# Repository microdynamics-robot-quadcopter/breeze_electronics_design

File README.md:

# breeze_electronics_design

## Description
This project is created and managed by EDA softwares, which contains the breeze quadcopter's component library, footprint library, schematic, printed circuit boards, etc.

## Note
Because of the changes in the project's requirements, we decided to use **Altium Designer** as the tool for developing the first edition of PCB rather than **KiCad**! So if you want to find the latest PCB design documents, please visit the **altium** directory.

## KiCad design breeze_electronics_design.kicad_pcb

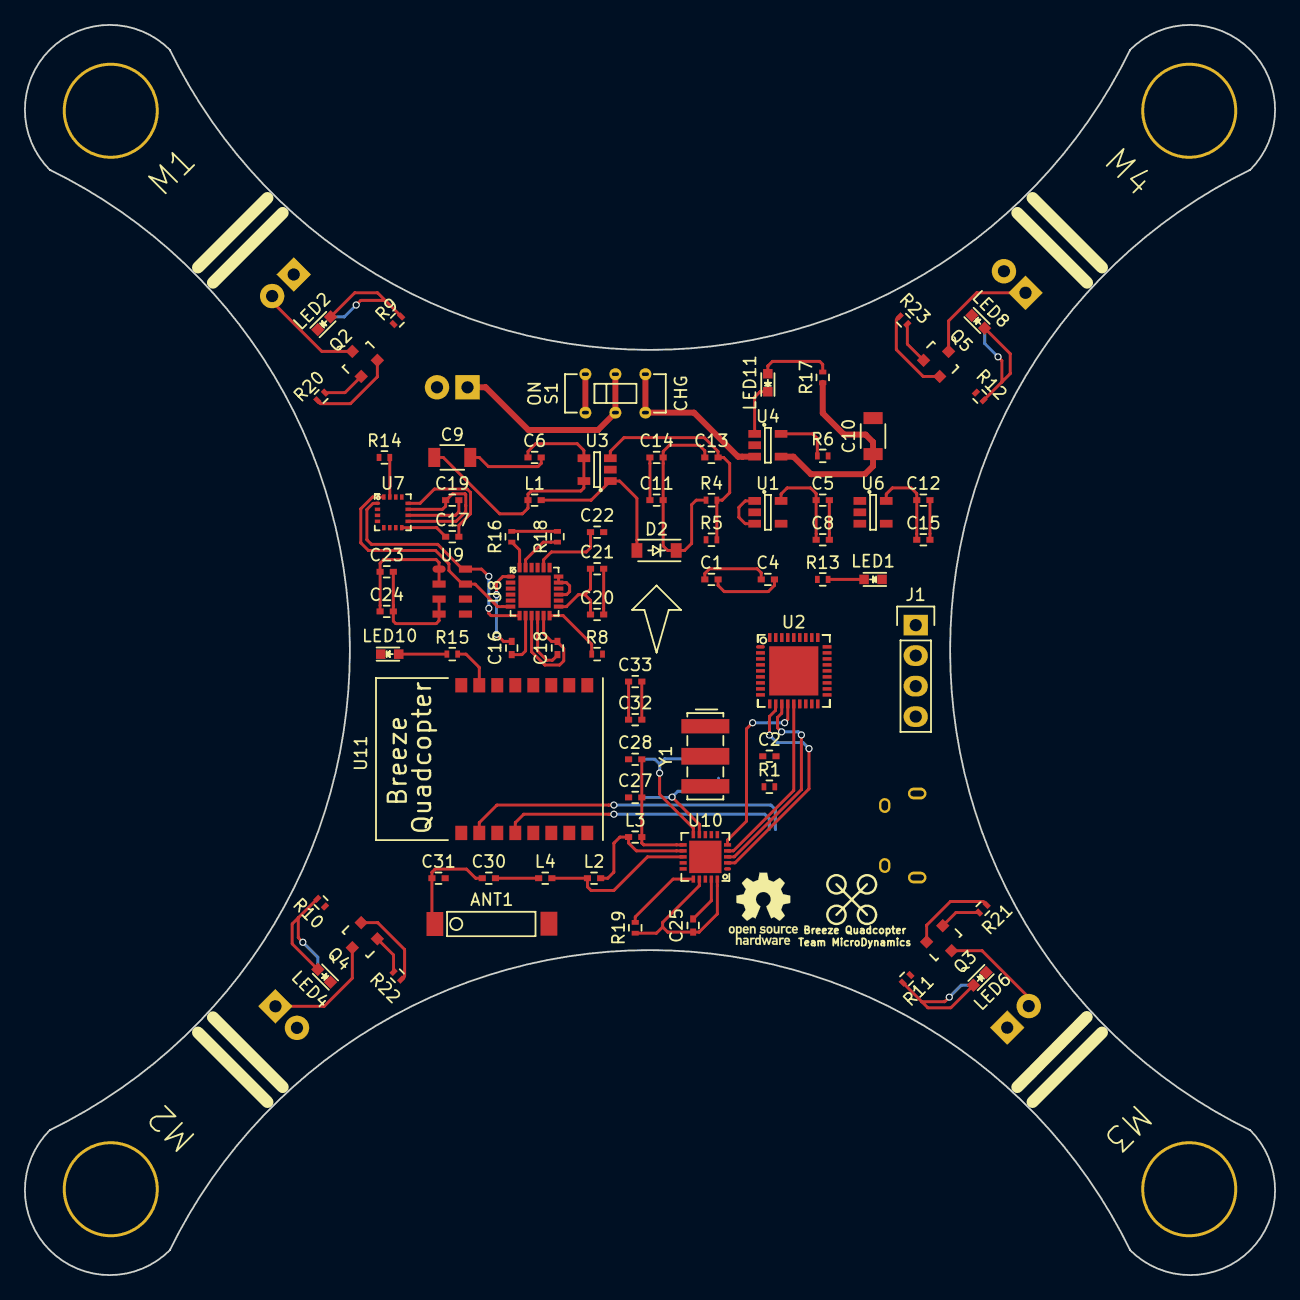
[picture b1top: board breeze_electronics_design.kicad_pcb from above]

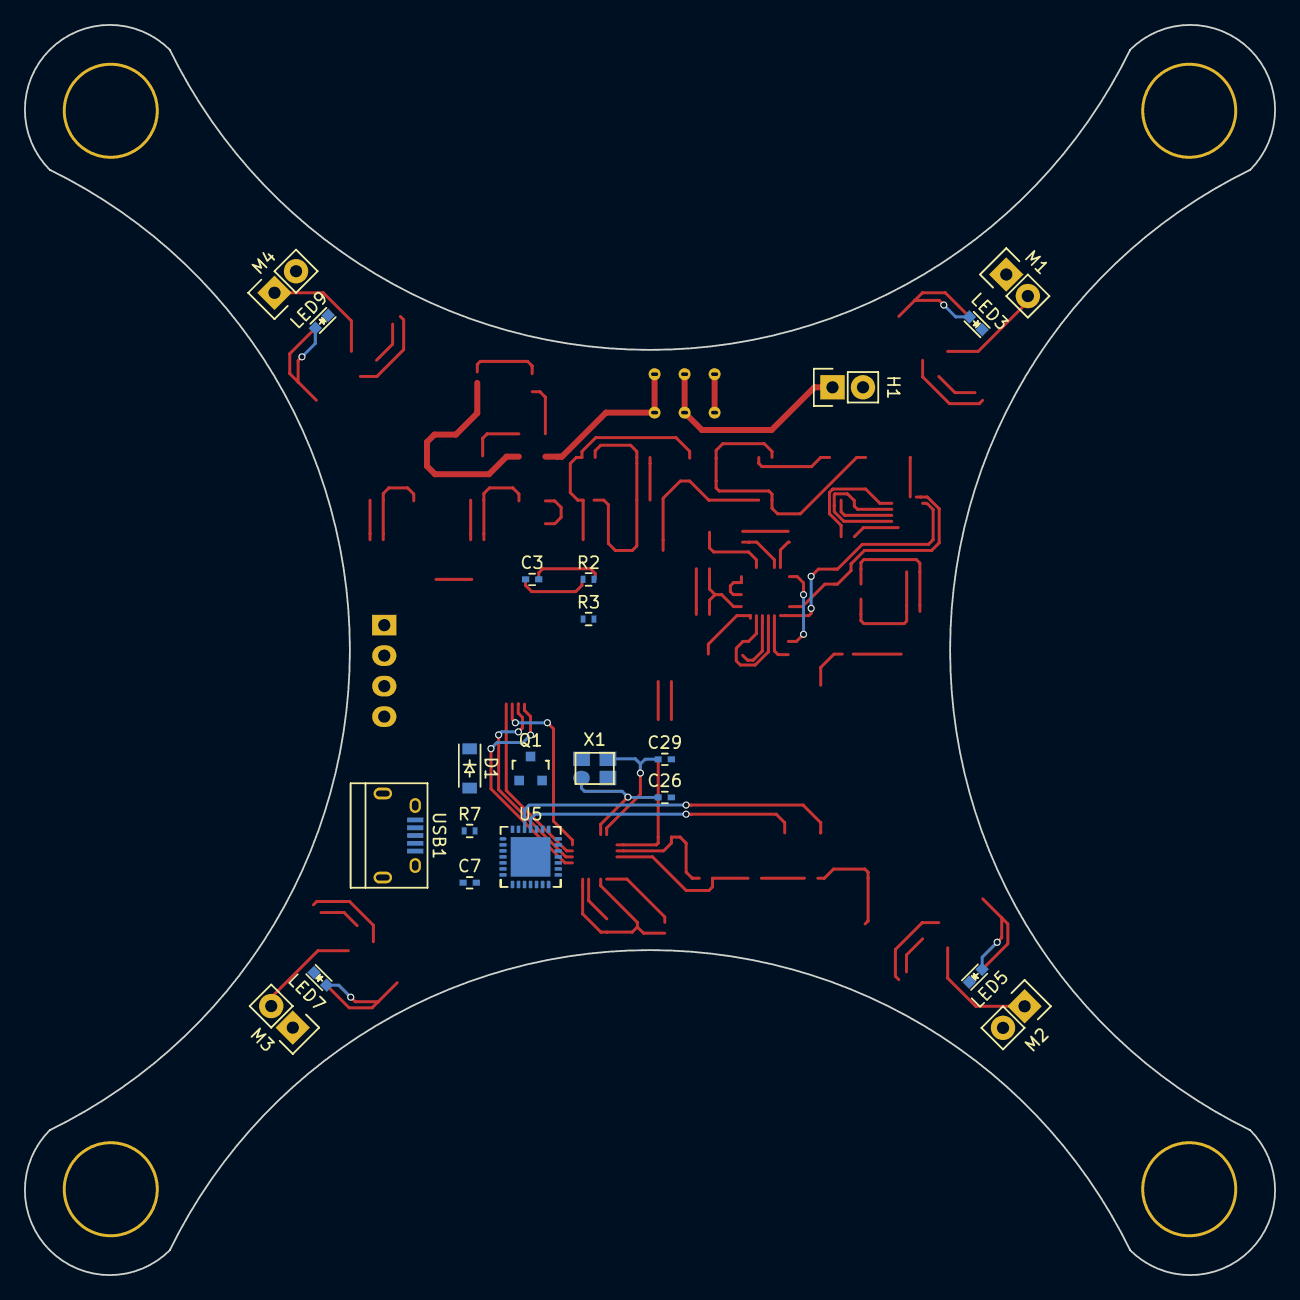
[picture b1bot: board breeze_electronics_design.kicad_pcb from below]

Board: 2 copper layers, 104.1 x 104.1 mm, 100 parts (21 on the bottom side), 100 nets.

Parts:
ANT1: Antenna; SMD_AN9520
C1, C6, C8, C11, C15, C18, C24, C32: 0.1UF; C_0402
C2, C3, C4, C5, C7, C12, C14, C16, C20, C21, C23, C25, C33: 2.2UF; C_0402
C9, C10: 10UF; C_1206
C13: 220PF; C_0402
C17: 220NF; C_0402
C19: 4.7UF; C_0402
C22, C27: 2.2NF; C_0402
C26, C29: 22PF; C_0402
C28: 4.7PF; C_0402
C30: 1.5PF; C_0402
C31: 1PF; C_0402
D1, D2: MBR0520; SOD-123
H1: Header; Pin_Header_Straight_1x02
J1: SIP4; Pin_Header_Straight_1x04
L1: 4.7UH; SMD_L0402
L2: 8.2NH; SMD_L0402
L3: 2.7NH; SMD_L0402
L4: 3.9NH; SMD_L0402
LED1: POWER; LED_0603
LED2: M1_LED_TOP; LED_0603
LED3: M1_LED_BOT; LED_0603
LED4: M2_LED_TOP; LED_0603
LED5: M2_LED_BOT; LED_0603
LED6: M3_LED_TOP; LED_0603
LED7: M3_LED_BOT; LED_0603
LED8: M4_LED_TOP; LED_0603
LED9: M4_LED_BOT; LED_0603
LED10: BT_LED; LED_0603
LED11: CHG_LED; LED_0603
M1, M3: MotorA; Pin_Header_Straight_1x02
M2, M4: MotorB; Pin_Header_Straight_1x02
Q1: S8050; SOT-23
Q2, Q3, Q4, Q5: SI2302; SOT-23
R1, R5, R7, R13: 10K; R_0402
R2, R3, R4, R20, R21, R22, R23: 33K; R_0402
R6: 1.65K; R_0402
R8, R14, R16, R18: 3K; R_0402
R9, R10, R11, R12, R15, R17: 100; R_0402
R19: 22K; R_0402
S1: SW2X3; DIP_SW2x3
U1: MIC5205-3.3; SOT-23-5
U2: STM32F103T8U6TR; VFQFPN_STM32F103T8U6TR
U3: LM27313; SOT-23-5
U4: LTC4054; SOT-23-5
U5: CP2102; QFN_CP2102
U6: MIC5205; SOT-23-5
U7: HMC5883L; LPCC_HMC5883L
U8: MPU6050; QFN_MPU6050
U9: MS5611; QFN_MS5611
U10: NRF24L01; QFN_NRF24L01
U11: HM_Bluetooth; SMD_HM
USB1: MicroUSB; USB_Micro-B
X1: 16MHZ; SMD_XTAL3225
Y1: 8MHZ; Resonator_7.2x3mm

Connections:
/ANT1: L2.1, L3.2, U10.12
/ANT2: L2.2, L4.1, U10.13
/BAT_DET: C3.1, R2.1, R3.1, U2.15
/BOOT0: Q1.3, R7.2, U2.35
/BT_EN: U2.17, U6.3
/BT_LED: R15.1, U11.15
/CE: U2.24, U10.1
/CHG_LED: LED11.1, U4.1
/CSN: U2.11, U10.2
/DN: U5.5, USB1.2
/DP: U5.4, USB1.3
/HM_INT: R14.2, U2.31, U7.15
/I2C_SCL: R18.2, U2.33, U8.23
/I2C_SDA: R16.2, U2.34, U8.24
/MISO: U2.13, U10.5
/MOSI: U2.14, U10.4
/MP_INT: R8.1, U2.32, U8.12
/NRF_IRQ: U2.29, U10.6
/OSC_IN: U2.2, Y1.1
/OSC_OUT: U2.3, Y1.3
/PA8: R10.1, U2.20
/PA11: R9.1, U2.23
/PB1: R11.1, U2.16
/PB3: R12.1, U2.30
/PWMA: Q2.1, R20.1, U2.7
/PWMB: Q4.1, R22.1, U2.8
/PWMC: Q3.1, R21.1, U2.9
/PWMD: Q5.1, R23.1, U2.10
/Q_SCK: U7.1, U8.7, U9.8
/Q_SDA: U7.16, U8.6, U9.7
/RST: C2.1, R1.2, U2.4, U5.24
/RXD_BT: U2.22, U5.26, U11.2
/S1: S1.1, S1.6
/S3: S1.3, S1.4, U4.3
/SCK: U2.12, U10.3
/SETC: C17.2, U7.12
/SWCLK: J1.1, U2.28
/SWDIO: J1.2, U2.25
/TXD_BT: U2.21, U5.25, U11.4
/VBAT: H1.1, S1.2, S1.5
/VBUS: C10.1, D1.2, R7.1, R17.1, U4.4, U5.7, U5.8, USB1.1
unnamed: ANT1.1, C30.2, C31.1
unnamed: C1.1, C4.1
unnamed: C1.2, C4.2
unnamed: C5.1, C8.1, U1.5
unnamed: C5.2, C8.2
unnamed: C6.1, C9.1, L1.1, U3.4, U3.5
unnamed: C6.2, C9.2
unnamed: C7.1, U5.3
unnamed: C7.2, U5.6
unnamed: C11.1, C13.1, C14.1, D2.1, R4.1
unnamed: C11.2, C14.2
unnamed: C12.1, C15.1, U6.5
unnamed: C12.2, C15.2
unnamed: C13.2, R4.2, R5.1, U3.3
unnamed: C16.1, U8.1
unnamed: C16.2, U8.8
unnamed: C17.1, U7.8
unnamed: C18.1, U8.10
unnamed: C18.2, U8.9, U8.11
unnamed: C19.1, U7.9, U7.11
unnamed: C19.2, U7.10
unnamed: C20.1, C21.1, U8.13
unnamed: C20.2, C21.2
unnamed: C22.1, U8.20
unnamed: C23.1, C24.1, U9.1, U9.2
unnamed: C23.2, C24.2, U9.3, U9.4
unnamed: C25.1, R19.1, U10.17, U10.20
unnamed: C25.2, U10.19
unnamed: C26.1, U10.9, X1.1
unnamed: C27.1, C28.1, L3.1, U10.11
unnamed: C29.2, U10.10, X1.3
unnamed: C30.1, L4.2
unnamed: C32.1, C33.1
unnamed: C32.2, C33.2
unnamed: D2.2, L1.2, U3.1
unnamed: LED1.2, R13.2
unnamed: LED2.1, LED3.1, LED4.1, LED5.1, LED6.1, LED7.1, LED8.1, LED9.1
unnamed: LED2.2, LED3.2, R9.2
unnamed: LED4.2, LED5.2, R10.2
unnamed: LED6.2, LED7.2, R11.2
unnamed: LED8.2, LED9.2, R12.2
unnamed: LED10.2, R15.2
unnamed: LED11.2, R17.2
unnamed: M1.2, Q2.3
unnamed: M2.1, Q4.3
unnamed: M3.2, Q3.3
unnamed: M4.1, Q5.3
unnamed: Q1.1, U5.28
unnamed: Q2.2, R20.2
unnamed: Q3.2, R21.2
unnamed: Q4.2, R22.2
unnamed: Q5.2, R23.2
unnamed: R6.1, U4.5
unnamed: R16.1, R18.1
unnamed: R19.2, U10.16
unnamed: U1.1, U1.3
unnamed: U2.1, U2.6
unnamed: U2.19, U2.27
unnamed: U8.15, U8.17, U8.18

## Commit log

2016-08-14 Add breeze_electronics_design project
2016-08-14 Add breeze_electronics_design component
2016-08-15 Finish the component library
2016-08-15 Modify the STM32F103T8U6TR
2016-08-15 Finish STM32F103T8U6TR connect
2016-08-16 Finish the basic schematic
2016-08-17 Modify the schematic of controller
2016-08-17 Modify the schematic of leds
2016-08-17 Modify the schematic of usb_to_serial
2016-08-17 Modify the schematic of wireless
2016-08-18 Modify the schematic of motor
2016-08-18 Modify the schematic of sensor
2016-08-18 Modify the schematic of power
2016-08-18 Fix some ERC's errors
2016-08-18 Add voltage and accuracy fields
2016-08-18 Modify the format of components
2016-08-18 Finish the schematic
2016-08-18 Add schematic's pdf
2016-08-18 Add schematic's image
2016-08-19 Add some informations
2016-08-19 Modify the component's text
2016-08-19 Add some parts of footprint
2016-08-20 Fix HMC5883L's name
2016-08-21 Modify the center of QFN to pad
2016-08-21 Modify the HM-06-BT
2016-08-22 Add the footprint of DIP_SW2x3
2016-08-22 Add the footprint of LPCC_HMC5883L
2016-08-22 Add the footprint of QFN_MPU6050
2016-08-22 Add the footprint of QFN_MS5611
2016-08-22 Add the footprint of SMD_AN9520
2016-08-22 Add the footprint of SMD_HM
2016-08-22 Add the footprint of SMD_L0402
2016-08-22 Add the footprint of SMD_XTAL3225
2016-08-22 Modify the footprint of QFN_CP2102
2016-08-22 Modify the footprint of QFN_NRF24L01
2016-08-22 Modify the footprint of VFQFPN_STM32F103T8U6TR
2016-08-22 Modify the power's name
2016-08-22 Modify the keywords
2016-08-22 Modify the schematic of MCU
2016-08-23 Modify the schematic of Serial
2016-08-23 Modify the schematic of Sensors
2016-08-23 Modify the schematic of Motors
2016-08-23 Fix schematic's name bug
2016-08-23 Format the description and keywords
2016-08-23 Modify the description and keywords
2016-08-23 Update the schematic's image and pdf
2016-08-24 Fix pin's number bug
2016-08-24 Modify the power and components' position
2016-08-25 Add the shape of breeze in PCB
2016-08-25 Modify the clearance of footprint's name
2016-08-25 Add the motor's base
2016-08-26 Add the Description
2016-08-26 Finish the layout of LEDs and Motors
2016-08-26 Modify the thick of courtyard line
2016-08-26 Finish the layout of Wireless
2016-08-26 Finish the layout of Sensors
2016-08-26 Finish the layout of Power
2016-08-26 Modify the line's length of GND
2016-08-27 Finish the layout of PCB
2016-08-27 Add the footprint of LOGO_Arrow
2016-08-27 Fix some bugs
2016-08-27 Update the image and pdf
2016-08-27 Modify the location of footprint's value
2016-08-27 Add the description and keywords
2016-08-28 Modify the REF**
2016-08-28 Add the footprint of LOGO_Project
2016-08-28 Finish the basic check of layout
2016-08-28 Modify the REF** of LOGO_Arrow
2016-08-29 Finish the basic wiring of LEDs
2016-08-29 Modify the GND from pin to component
2016-08-30 Relocate the footprints of Wireless
2016-08-30 Modify the redundant line
2016-08-30 Modify the footprints of Sensors
2016-08-30 Relocate the footprints of Power
2016-08-31 Relocate the footprints of MCU and Serial
2016-08-31 Make the module of Serial to the pcb's back
2016-09-01 Modify the size
2016-09-12 Modify the location of sentence
2016-09-12 Modify the clearance from 0.2 to 0.15
2016-09-13 Modify the size of logo
2016-09-13 Adjust the layout of Sensor module
2016-09-13 Add bold outline
2016-09-13 Finish the major layout
2016-09-13 Move the PCB to the center of drawing
2016-09-13 Finish the automatic routing of Motors
2016-09-16 Finish the wiring of Motors
2016-09-17 Modify the wiring's layout of Motors
2016-09-17 Modify the layout of footprints accurately
2016-09-18 Finish the layout of all footprints
2016-09-18 Fix pin's dislocation of NRF24L01
2016-09-18 Finish the wiring of Wireless
2016-09-18 Finish the major wiring of Sensors
2016-09-18 Update documents
2016-09-18 Update images
2016-09-18 Finish the major wiring of Power
2016-09-19 Add the part of PCB
2016-09-19 Update the project's date
2016-09-19 Add new documents and images
2016-09-19 Modify the image of pcb to approx scale
2016-09-19 Fix the name's error
2017-01-14 Format the kicad's project of breeze_std
2017-01-14 Add the README.md
2017-01-14 Rename the images
2017-01-14 Modify the name of project
2017-01-16 Add LICENSE
2017-01-17 Readjust the organization of project
2017-01-17 Modify the README.md
2017-01-23 Add motor circuit in cadence design
2017-01-23 Add schematic library and NRF24L01 part
2017-01-23 Add HM-06-BT part
2017-01-23 Add MS5611 part
2017-01-24 Add MPU9250 part
2017-01-24 Add STM32F405RGT6 part
2017-01-24 Add AN9520-245 part and modify circuit
2017-01-24 Draw wireless circuit
2017-01-24 Draw LED circuit
2017-01-25 Draw senor circuit
2017-01-25 Draw cpu circuit
2017-01-25 Draw all circuit
2017-01-26 Check all circuit
2017-01-28 Draw all schematic
2017-01-28 Add circuit footprint
2017-01-28 Stop circuit design temporarily
2017-01-30 Add the project
2017-02-02 Add the .gitignore
2017-02-02 Add the library
2017-02-02 Add the template
2017-02-15 Finish the template
2017-02-15 Rename the suffix
2017-02-15 Add the schematics
2017-02-15 Save the project
2017-02-15 Finish the information
2017-02-22 Add the component of MPU6050
2017-02-22 Add the component of HMC5883L
2017-02-22 Add the component of MS611
2017-02-22 Add the component of NUF2221W1T2
2017-02-22 Add the component of MAX16054
2017-02-22 Add the component of BQ24075RGTR
2017-02-22 Add the component of TPS79301DBVR
2017-02-22 Add the component of nRF51822
2017-02-22 Add the component of CP2102
2017-02-22 Add the component of AN9520
2017-02-22 Add the component of RES-0603
2017-02-22 Add the component of CAP-0603
2017-02-22 Add the component of IND-0402
2017-02-22 Add the component of LED-0603
2017-02-22 Finish the all components
2017-02-23 Modify the BQ24075RGTR
2017-02-24 Add all footprints
2017-02-24 Modify the USB_MICRO
2017-02-24 Rename all schematics
2017-02-24 Add the description of all footprints
2017-02-24 Add all components to footprints
2017-02-25 Rename the scheamtic
2017-02-25 Finish the breeze_power schematic
2017-02-25 Fix the bug
2017-02-25 Adjust the location of files
2017-02-25 Add the Motor_A and Motor_B
2017-02-25 Add the HDRM-1X2
2017-02-25 Fix the directional bug for motors
2017-02-25 Fix the pin's bug of HMC5883L
2017-02-25 Finish the breeze_sensor schematic
2017-02-27 Adjust the width of text
2017-02-27 Finish the description
2017-02-27 Modify the net labels
2017-02-27 Modify the bugs
2017-02-27 Finish the breeze_wireless schematic
2017-02-27 Modify the STM32F103T6U6
2017-02-27 Modify the shape of components
2017-02-27 Adjust the GND and VCC
2017-02-28 Add the description of breeze_power schematic
2017-02-28 Update the project
2017-02-28 Modify the name of Net Labels
2017-02-28 Modify the USART Net Label
2017-02-28 Finish the breeze_controller schematic
2017-02-28 Adjust the size of Text Frame
2017-02-28 Add the description of breeze_controller schematic
2017-02-28 Ignore all .LOG files
2017-02-28 Finish the annotation
2017-02-28 Fix the warning of Net Labels
2017-02-28 Add the PCB file
2017-03-01 Add the image
2017-03-01 Update the template of schematic
2017-03-01 Update all schematics
2017-03-01 Rename the name of logo
2017-03-01 Add the logo
2017-03-01 Finish the template of pcb
2017-03-01 Update the template
2017-03-01 Add the breeze_pcb file
2017-03-02 Finish the shape of board
2017-03-02 Modify the Keep-Out Layer
2017-03-02 Add all footprints to breeze_pcb
2017-03-02 Rename the number of all components
2017-03-02 Add the order of annotation
2017-03-03 Finish the layout of motor
2017-03-03 Finish the layout of sensor
2017-03-03 Update the layout of sensor
2017-03-03 Modify the schematic
2017-03-04 Finish the layout of controller
2017-03-04 Modify the footprint of SKRELGE010 and SOD-523
2017-03-04 Adjust the net label of switchs
2017-03-04 Modify the number of Battery
2017-03-04 Check all the layouts
2017-03-04 Add the MSS-22D18G2 and fix some bugs
2017-03-04 Modify the schematic of switch
2017-03-04 Import the changes
2017-03-04 Modify the layouts
2017-03-05 Add the logos
2017-03-05 Embedded logo to schematic's template
2017-03-05 Finish the layouts
2017-03-05 Add the Note
2017-03-05 Add the setup.bat
2017-03-05 Add the badges
2017-03-05 Fix the bug of blank space
2017-03-05 Export the pdf
2017-03-06 Set the rules
2017-03-06 Update the file
2017-03-06 Add the line of Mechanical 15
2017-03-06 Update the footprints
2017-03-06 Fix the collision of components at the bottom layer
2017-03-06 Fix the collision of components at the top layer
2017-03-06 Fix all the collisions
2017-03-07 Update the footprint of LPCC-16 and QFN-24
2017-03-07 Fix the bug of clearance constraints
2017-03-07 Finish the basic route on the top layer
2017-03-07 Finish all routes on the top layer
2017-03-07 Update the VFQFPN-36
2017-03-07 Finish the basic routes on the bottom layer
2017-03-07 Finish the route of +BAT bus
2017-03-08 Adjust the net labels of pins
2017-03-08 Finish the bus's route on the top layer
2017-03-08 Swap the positions of two net labels
2017-03-08 Finish the major routes
2017-03-09 Finish some routes
2017-03-10 Finish all routes
2017-03-10 Check some routes
2017-03-11 Check all routes
2017-03-11 Finish the plane split
2017-03-11 Finish the region
2017-03-11 Finish all tasks before placing polygon
2017-03-12 Finish the copper of AGND
2017-03-12 Finish the copper of DGND on top layer
2017-03-12 Finish the copper of DGND on bottom layer
2017-03-12 Modify the size of via
2017-03-12 Fix some violations
2017-03-12 Fix an un-routed bug
2017-03-12 Fix double un-routed bugs
2017-03-12 Fix the bug of isolated copper
2017-03-12 Add teardrops to all pads
2017-03-12 Add the BOM
2017-03-12 Add the pdf
2017-03-12 Add all pdf
2017-03-12 Add all images
2017-03-12 Add all images to README.md
2017-03-12 Add the badge of version
2017-12-04 Add output files
2017-12-15 Remove output files
2017-12-15 Modify the project
